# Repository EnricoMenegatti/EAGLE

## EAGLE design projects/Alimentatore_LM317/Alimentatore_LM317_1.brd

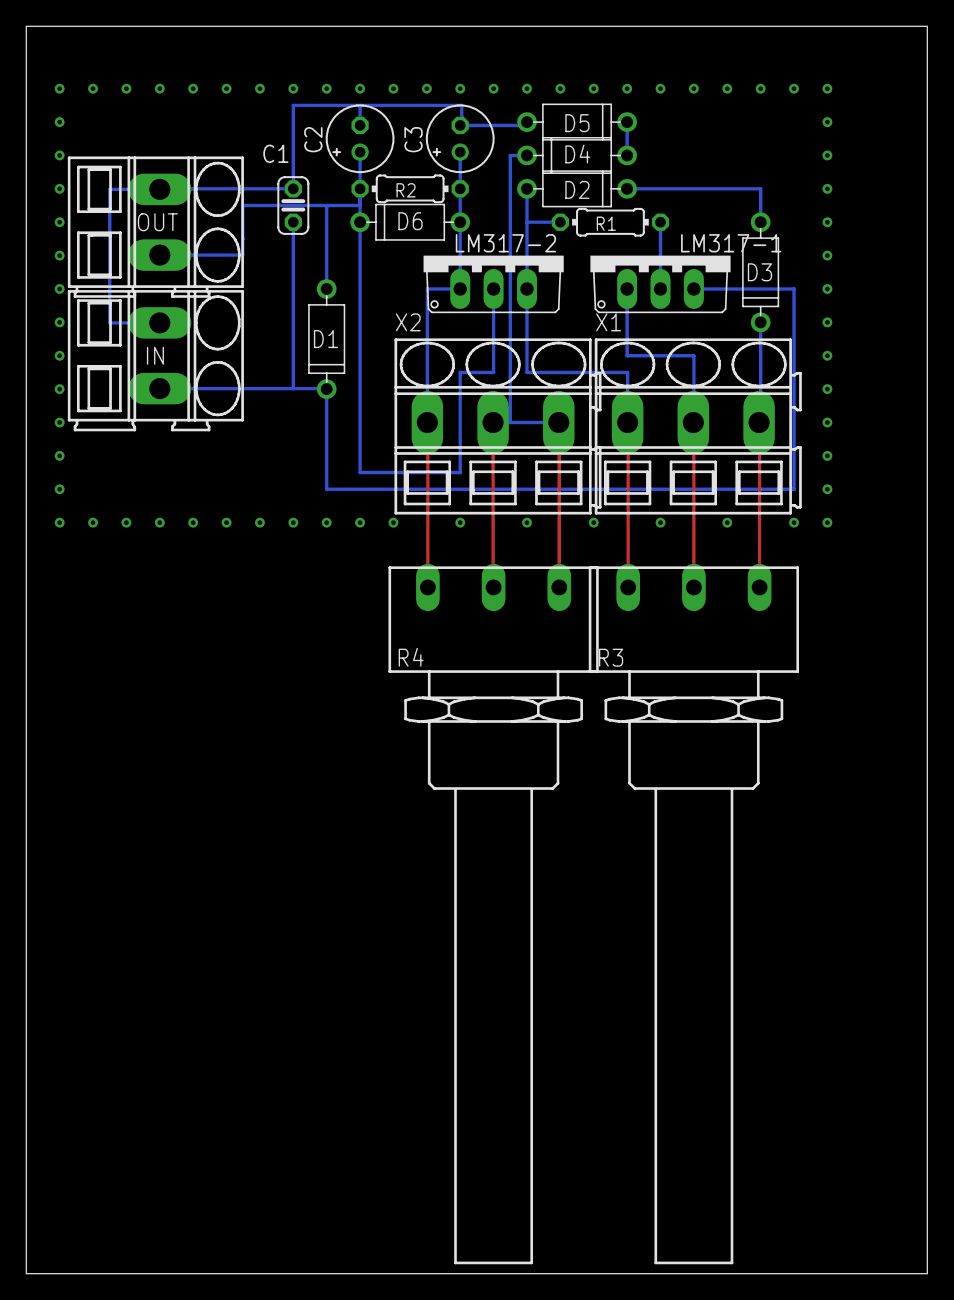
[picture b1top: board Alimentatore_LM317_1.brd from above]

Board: 2 copper layers, 68.6 x 94.9 mm, 19 parts (0 on the bottom side), 11 nets.

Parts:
C1: 0.1uF; C025-024X044
C2: 10uF Tant.; E2-5
C3: 10uF; E2-5
D1: 1N4002; DIOAD860W70L460D235B
D2, D3, D4, D5, D6: 1N4001; DIOAD860W70L460D235B
IN: SMKDSP_1,5/2
LM317-1, LM317-2: TO220V
OUT: SMKDSP_1,5/2
R1: 0204/7
R2: 240; 0204/7
R3: 1k; PC16S
R4: 5k; PC16S
X1, X2: SMKDSP_1,5/3

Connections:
GND: C1.2, C2.-, C3.-, D5.2, IN.1, OUT.1
unnamed: C2.+, D1.2, D6.1, LM317-2.2, OUT.2, R2.1
unnamed: LM317-1.2, R1.2
unnamed: D2.2, LM317-2.3, R1.1, R3.1A, X1.1
unnamed: D2.1, D3.2
unnamed: LM317-1.1, R3.1S, X1.2
unnamed: D4.2, D5.1
unnamed: D3.1, R3.1E, X1.3
unnamed: C3.+, D6.2, LM317-2.1, R2.2, R4.1A, X2.1
unnamed: D4.1, R4.1E, R4.1S, X2.2, X2.3
VCC: C1.1, D1.1, IN.2, LM317-1.3

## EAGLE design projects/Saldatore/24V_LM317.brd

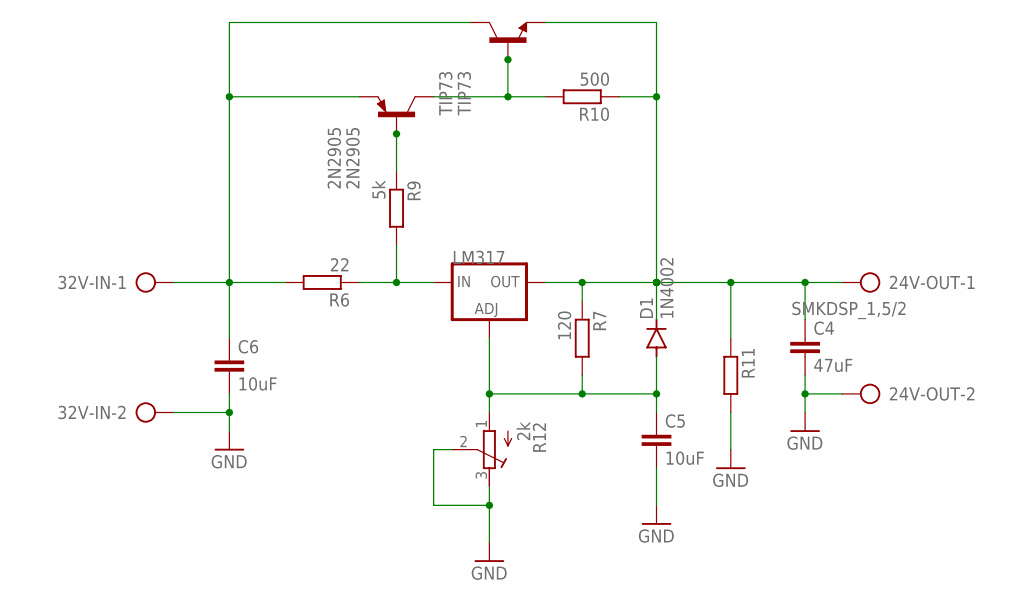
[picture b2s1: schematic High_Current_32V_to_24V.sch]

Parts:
2N2905: 2N2905; TO39
24V-OUT, 32V-IN: SMKDSP_1,5/2
C4: 47uF; C025-025X050
C5, C6: 10uF; C025-025X050
D1: 1N4002; DIOAD860W70L460D235B
LM317: LM317TS317TS_TO220; TO220V
R6: 22; 0204/7
R7: 120; 0204/7
R9: 5k; 0204/7
R10: 500; 0204/7
R11: R-EU_0204/7; 0204/7
R12: 2k; RTRIM64W
TIP73: TIP73; TO5

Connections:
24V: 24V-OUT.1, C4.1, D1.1 (C), LM317.2 (OUT), R7.1, R10.1, R11.1, TIP73.1 (E)
GND: 24V-OUT.2, 32V-IN.2, C4.2, C5.2, C6.2, R11.2, R12.2 (S), R12.3 (E)
unnamed: LM317.3 (IN), R6.1, R9.2
unnamed: 2N2905.2 (B), R9.1
unnamed: 2N2905.3 (C), R10.2, TIP73.2 (B)
unnamed: 2N2905.1 (E), 32V-IN.1, C6.1, R6.2, TIP73.3 (C)
unnamed: C5.1, D1.2 (A), LM317.1 (ADJ), R7.2, R12.1 (A)

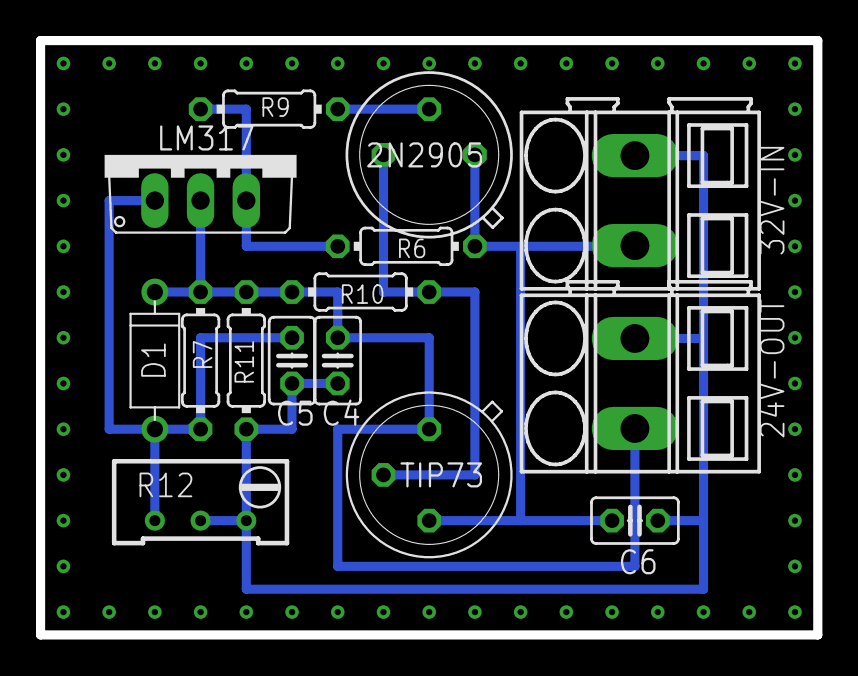
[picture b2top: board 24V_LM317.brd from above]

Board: 2 copper layers, 43.2 x 33.0 mm, 15 parts (0 on the bottom side), 7 nets.

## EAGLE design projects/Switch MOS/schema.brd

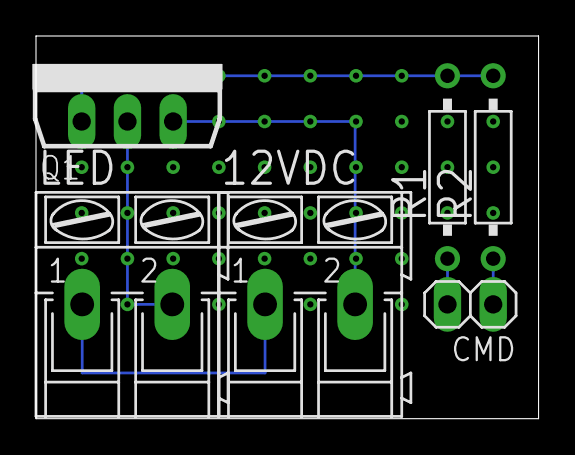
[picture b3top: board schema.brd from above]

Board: 2 copper layers, 27.9 x 21.3 mm, 6 parts (0 on the bottom side), 6 nets.

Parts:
12VDC: AK300/2
CMD: 1X02
LED: AK300/2
Q1: IRF3704L-V; TO262-V
R1: 270; RS1/4
R2: 10k; RS1/4

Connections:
unnamed: CMD.2, R1.1
unnamed: Q1.1, R1.2, R2.2
unnamed: CMD.1, R2.1
unnamed: 12VDC.1, LED.1
unnamed: LED.2, Q1.2
unnamed: 12VDC.2, Q1.3
